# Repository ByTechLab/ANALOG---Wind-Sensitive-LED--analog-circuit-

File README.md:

<div align="center">
    
</div>

Wind sensitive LED (analog circuit)

### Read more at BYTECHLAB:

<table style="width: 100%; border: none;" cellspacing="0" cellpadding="0" border="0">
  <tr>
    <td></td>
    <td>https://bytechlab.com/2018/09/an-led-you-can-blow-out-like-a-candle/</td>
  </tr>
</table>

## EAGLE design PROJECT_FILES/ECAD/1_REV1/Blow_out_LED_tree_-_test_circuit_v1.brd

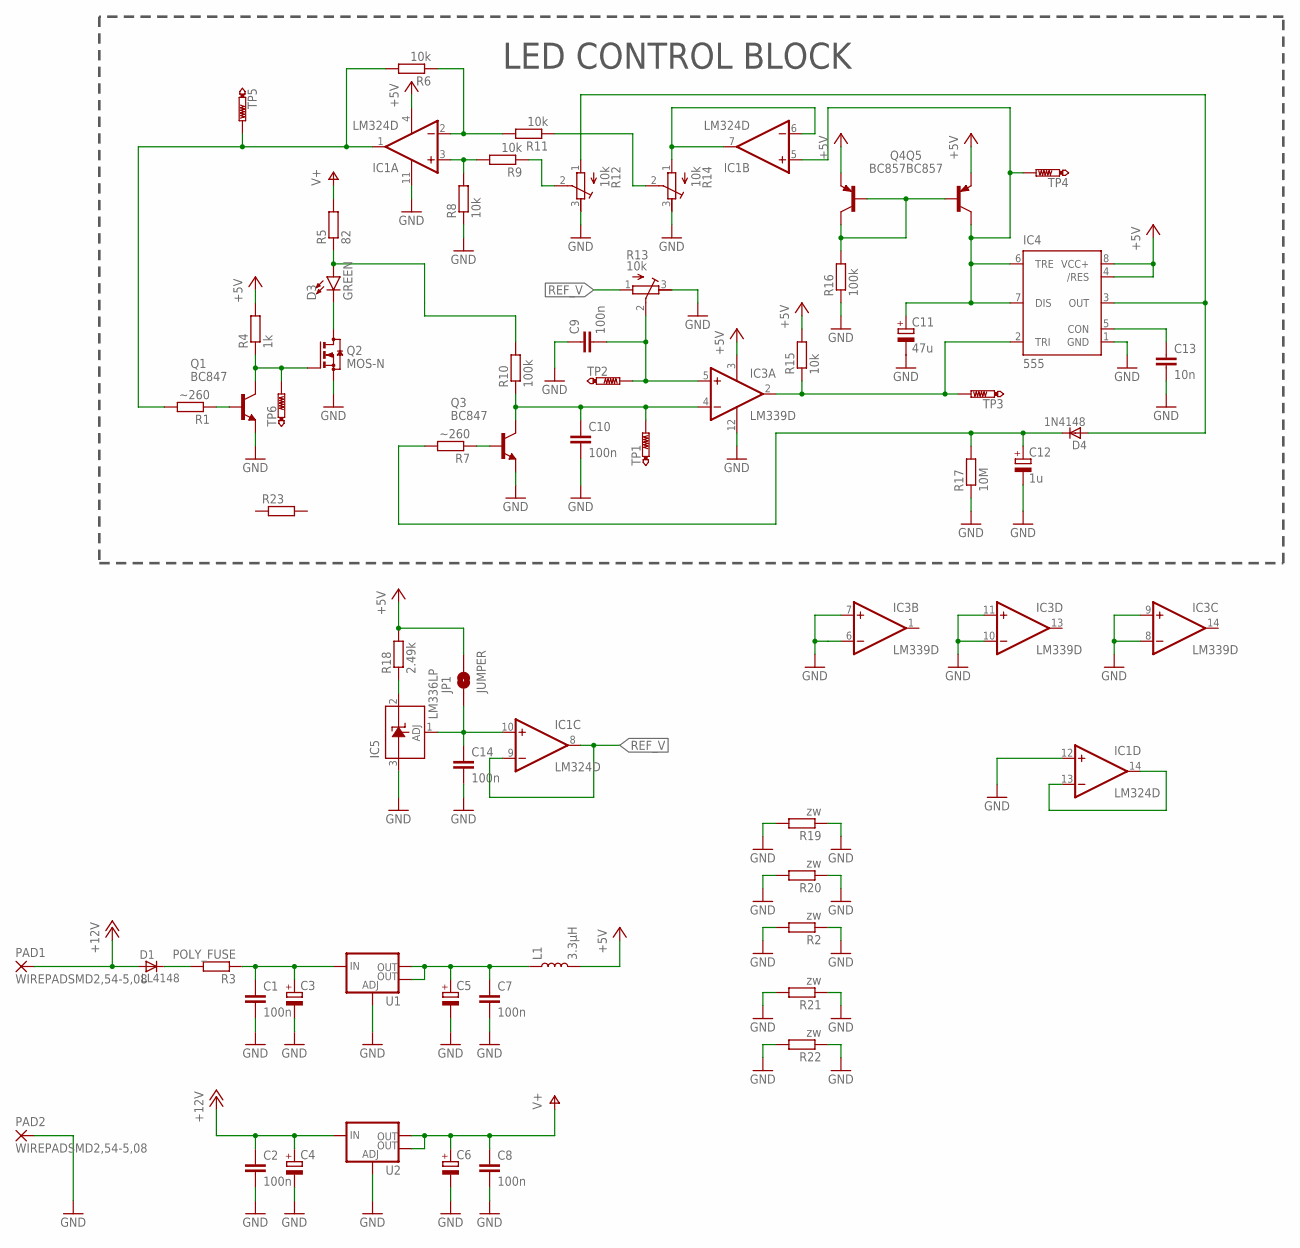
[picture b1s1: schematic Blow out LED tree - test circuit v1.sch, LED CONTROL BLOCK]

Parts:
C1, C2, C7, C8, C9, C10, C14: 100n; C1206
C3, C4, C5, C6: CPOL-EU153CLV-0810; 153CLV-0810
C11: 47u; 153CLV-0605
C12: 1u; 153CLV-0605
C13: 10n; C1206
D1: LL4148; SOD80_DO213AA_MINIMELF
D3: GREEN; FKIT-LED-1206
D4: 1N4148; SOD80_DO213AA_MINIMELF
IC1: LM324D; SO14
IC3: LM339D; SO14
IC4: 555; SO08
IC5: LM336LP; TO92
JP1: JUMPER; SMT-JUMPER_2_NO_NO-SILK_ROUND
L1: 3.3µH; 0805
PAD1, PAD2: WIREPADSMD2,54-5,08; SMD2,54-5,08
Q1, Q3: BC847; SOT23
Q2: MOS-N; SOT23
Q4, Q5: BC857; SOT23-BEC
R1, R7: ~260; R1206
R2, R19, R20, R21, R22: zw; R1206
R3: POLY_FUSE; R1206
R4: 1k; R1206
R5: 82; R1206
R6, R8, R9, R11, R15: 10k; R1206
R10, R16: 100k; R1206
R12, R13, R14: 10k; RTRIM3374
R17: 10M; R1206
R18: 2.49k; R1206
R23: R-EU_R0603; R0603
TP1, TP2, TP3, TP4, TP5, TP6: PTR1B2,54; B2,54
U1, U2: V_REG_LM1117SOT223; SOT223

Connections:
+5V: IC1.4 (V+), IC3.3 (V+), IC4.4 (/RES), IC4.8 (VCC+), JP1.2, L1.2, Q4.E, Q5.E, R4.2, R15.2, R18.2
+12V: C2.1, C4.+, D1.A, PAD1.1, U2.3 (IN)
GND: C1.2, C2.2, C3.-, C4.-, C5.-, C6.-, C7.2, C8.2, C9.1, C10.2, C11.-, C12.-, C13.2, C14.2, IC1.11 (V-), IC1.12 (+IN), IC3.6 (-IN), IC3.7 (+IN), IC3.8 (-IN), IC3.9 (+IN), IC3.10 (-IN), IC3.11 (+IN), IC3.12 (GND), IC4.1 (GND), IC5.3 (A), PAD2.1, Q1.2 (E), Q2.2 (S), Q3.2 (E), R2.1, R2.2, R8.1, R12.3 (E), R13.3 (E), R14.3 (E), R16.1, R17.1, R19.1, R19.2, R20.1, R20.2, R21.1, R21.2, R22.1, R22.2, U1.1 (ADJ), U2.1 (ADJ)
unnamed: D3.A, R5.1, R10.2
unnamed: C14.1, IC1.10 (+IN), IC5.1 (ADJ), JP1.1
unnamed: C10.1, IC3.4 (-IN), Q3.3 (C), R10.1, TP1.TP
unnamed: C9.2, IC3.5 (+IN), R13.2 (S), TP2.TP
unnamed: Q3.1 (B), R7.1
unnamed: Q4.B, Q4.C, Q5.B, R16.2
unnamed: IC1.6 (-IN), IC1.7 (OUT), R14.1 (A)
unnamed: IC3.2 (OUT), IC4.2 (TRI), R15.1, TP3.TP
unnamed: C13.1, IC4.5 (CON)
unnamed: D4.A, IC4.3 (OUT), R12.1 (A)
unnamed: C12.+, D4.C, R7.2, R17.2
unnamed: IC1.3 (+IN), R8.2, R9.2
unnamed: C11.+, IC1.5 (+IN), IC4.6 (TRE), IC4.7 (DIS), Q5.C, TP4.TP
unnamed: IC1.2 (-IN), R6.1, R11.2
unnamed: IC1.1 (OUT), R1.2, R6.2, TP5.TP
unnamed: R11.1, R14.2 (S)
unnamed: R9.1, R12.2 (S)
unnamed: IC5.2 (C), R18.1
unnamed: Q1.3 (C), Q2.1 (G), R4.1, TP6.TP
unnamed: Q1.1 (B), R1.1
unnamed: IC1.13 (-IN), IC1.14 (OUT)
unnamed: D1.C, R3.2
unnamed: C1.1, C3.+, R3.1, U1.3 (IN)
unnamed: C5.+, C7.1, L1.1, U1.2 (OUT), U1.4 (OUT)
unnamed: D3.C, Q2.3 (D)
REF_V: IC1.8 (OUT), IC1.9 (-IN), R13.1 (A)
V+: C6.+, C8.1, R5.2, U2.2 (OUT), U2.4 (OUT)

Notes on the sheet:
LED CONTROL BLOCK

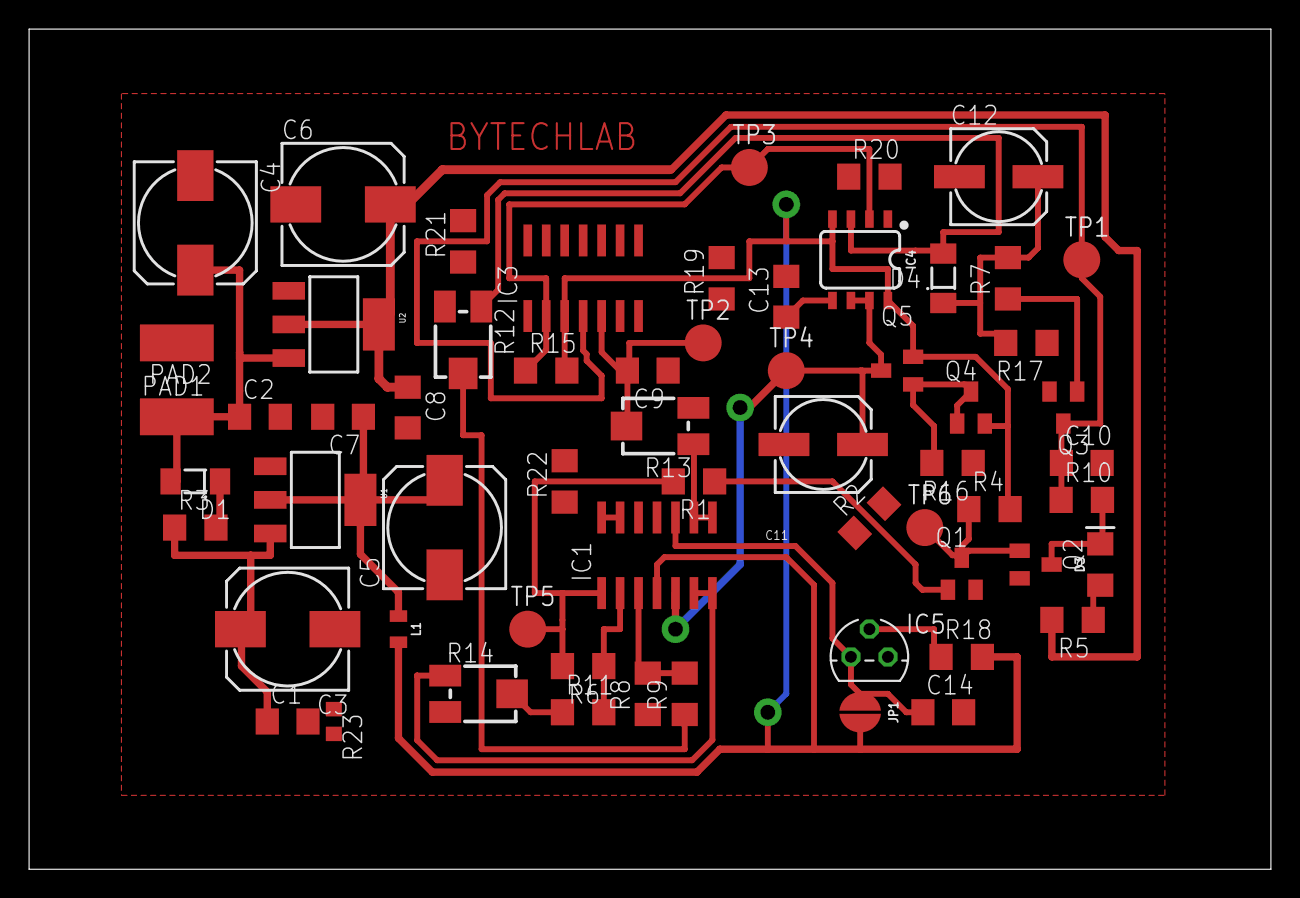
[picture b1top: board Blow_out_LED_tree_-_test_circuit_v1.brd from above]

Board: 2 copper layers, 85.4 x 57.8 mm, 61 parts (0 on the bottom side), 30 nets.

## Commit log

2024-11-10 Upload files
2025-08-17 Uplaod files

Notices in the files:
parts and their libraries:
SparkFun-LED: Licensing: Creative Commons ShareAlike 4.0 International - https://creativecommons.org/licenses/by-sa/4.0
